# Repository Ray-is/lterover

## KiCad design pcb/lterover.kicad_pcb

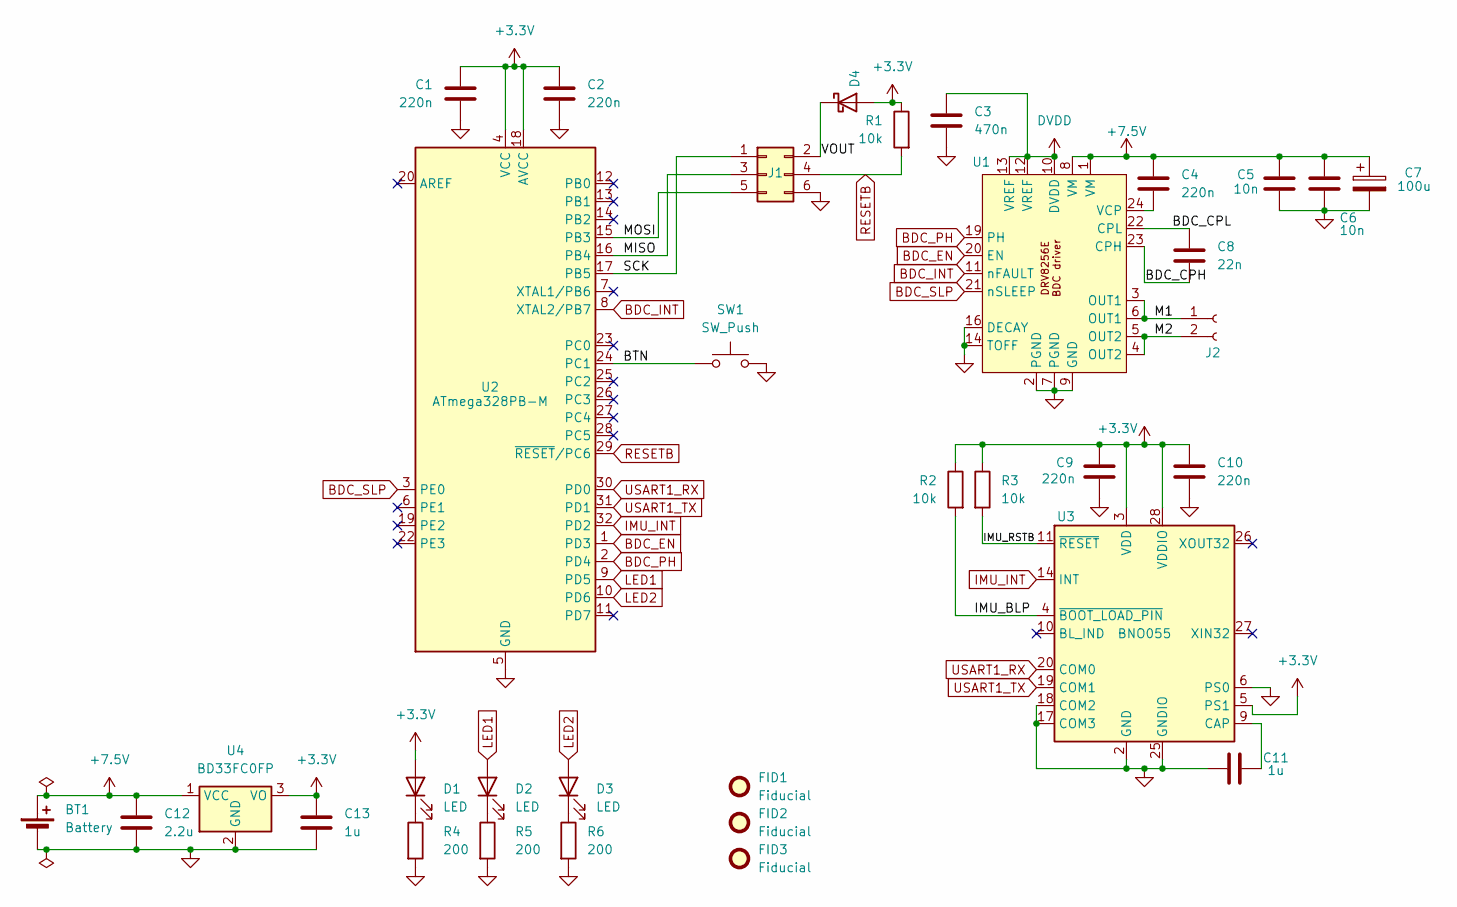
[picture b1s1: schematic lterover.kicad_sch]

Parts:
BT1: Battery; battery_2pad
C1, C2, C4, C9, C10: 220n; C_0402_1005Metric; MPN CL05B224KO5NNNC
C3: 470n; C_0402_1005Metric; MPN LMK105B7474KV-F
C5, C6: 10n; C_0201_0603Metric; MPN GRM033R71A103KA01D
C7: 100u; CP_Elec_5x5.4; MPN EEE-1AA101WAR
C8: 22n; C_0201_0603Metric; MPN EMK063B7223MP-F
C11, C13: 1u; C_0402_1005Metric; MPN 0402W105K100HI
C12: 2.2u; C_0603_1608Metric; MPN CL10B225KP8NNNC
D1, D2, D3: LED; LED_0402_1005Metric; MPN B18S1USD-05C000234U1930
D4: D_SOD-523; MPN RB521S30T1G
FID1, FID2, FID3: Fiducial; Fiducial_0.75mm_Mask1.5mm
J1: Conn_02x03_Odd_Even; PinHeader_2x03_P2.54mm_Vertical; MPN TSW-103-23-G-D
J2: Conn_01x02_Socket; JST_XH_B2B-XH-A_1x02_P2.50mm_Vertical; MPN B2B-XH-A
R1, R2, R3: 10k; R_0402_1005Metric; MPN RC0402FR-1310KL
R4, R5, R6: 200; R_0402_1005Metric; MPN RC0402FR-07200RL
SW1: SW_Push; SW_PUSH_6mm; MPN TS02-66-60-BK-260-SCR-D
U1: DRV8256E; VQFN-24-1EP_4x4mm_P0.5mm_EP2.5x2.5mm_ThermalVias; MPN DRV8256ERGER
U2: ATmega328PB-M; QFN-32-1EP_5x5mm_P0.5mm_EP3.1x3.1mm; MPN ATmega328PB-MU
U3: BNO055; LGA-28_5.2x3.8mm_P0.5mm; MPN BNO055
U4: BD33FC0FP; TO-252-2; MPN BD33FC0FP-E2

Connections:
+3.3V: C1.2, C2.2, C9.2, C10.2, C13.1, D1.2 (A), D4.2 (A), R1.1, R2.1, R3.1, U2.4 (VCC), U2.18 (AVCC), U3.3 (VDD), U3.5 (PS1), U3.28 (VDDIO), U4.3 (VO)
+7.5V: BT1.1 (+), C4.2, C5.2, C6.2, C7.1, C12.1, U1.1 (VM), U1.8 (VM), U4.1 (VCC)
/BDC_CPH: C8.1, U1.23 (CPH)
/BDC_CPL: C8.2, U1.22 (CPL)
/BTN: SW1.1, U2.24 (PC1)
/IMU_BLP: R2.2, U3.4 (~BOOT_LOAD_PIN)
/IMU_RSTB: R3.2, U3.11 (~RESET)
/M1: J2.1, U1.3 (OUT1), U1.6 (OUT1)
/M2: J2.2, U1.4 (OUT2), U1.5 (OUT2)
/MISO: J1.3, U2.16 (PB4)
/MOSI: J1.5, U2.15 (PB3)
/SCK: J1.1, U2.17 (PB5)
/VOUT: D4.1 (K), J1.2
BDC_EN: U1.20 (EN), U2.1 (PD3)
BDC_INT: U1.11 (nFAULT), U2.8 (XTAL2/PB7)
BDC_PH: U1.19 (PH), U2.2 (PD4)
BDC_SLP: U1.21 (nSLEEP), U2.3 (PE0)
DVDD: C3.2, U1.10 (DVDD), U1.12 (VREF), U1.13 (VREF)
GND: BT1.2 (-), C1.1, C2.1, C3.1, C5.1, C6.1, C7.2, C9.1, C10.1, C11.2, C12.2, C13.2, J1.6, R4.2, R5.2, R6.2, SW1.2, U1.2 (PGND), U1.7 (PGND), U1.9 (GND), U1.14 (TOFF), U1.16 (DECAY), U2.5 (GND), U2.21 (GND), U2.33 (GND), U3.2 (GND), U3.6 (PS0), U3.17 (COM3), U3.18 (COM2), U3.25 (GNDIO), U4.2 (GND)
IMU_INT: U2.32 (PD2), U3.14 (INT)
LED1: D2.2 (A), U2.9 (PD5)
LED2: D3.2 (A), U2.10 (PD6)
unnamed: D1.1 (K), R4.1
unnamed: D2.1 (K), R5.1
unnamed: D3.1 (K), R6.1
unnamed: C4.1, U1.24 (VCP)
unnamed: C11.1, U3.9 (CAP)
RESETB: J1.4, R1.2, U2.29 (~RESET/PC6)
USART1_RX: U2.30 (PD0), U3.20 (COM0)
USART1_TX: U2.31 (PD1), U3.19 (COM1)

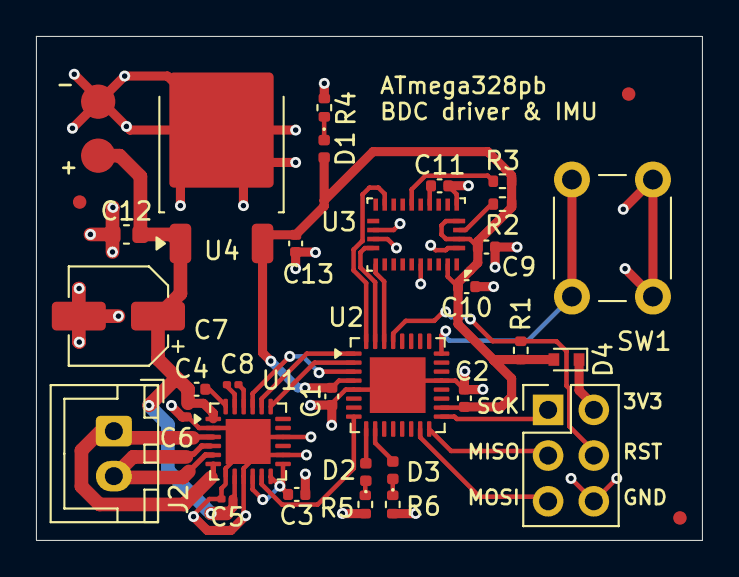
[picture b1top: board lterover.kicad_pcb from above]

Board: 2 copper layers, 37.0 x 28.0 mm, 34 parts (0 on the bottom side), 30 nets.

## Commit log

2026-01-12 First commit with files
2026-01-12 First commit with files 1
2026-01-12 Modified index.html
2026-01-13 Reorganized files, added KiCAD project and firmware folder
2026-01-20 Finished schematic and layout
2026-01-21 Finished PCB routing, deleted server for new project
2026-01-29 Finished PCB
